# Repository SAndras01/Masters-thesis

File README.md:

# Masters-thesis
Two-axes rotary table for characterization of accelerometers

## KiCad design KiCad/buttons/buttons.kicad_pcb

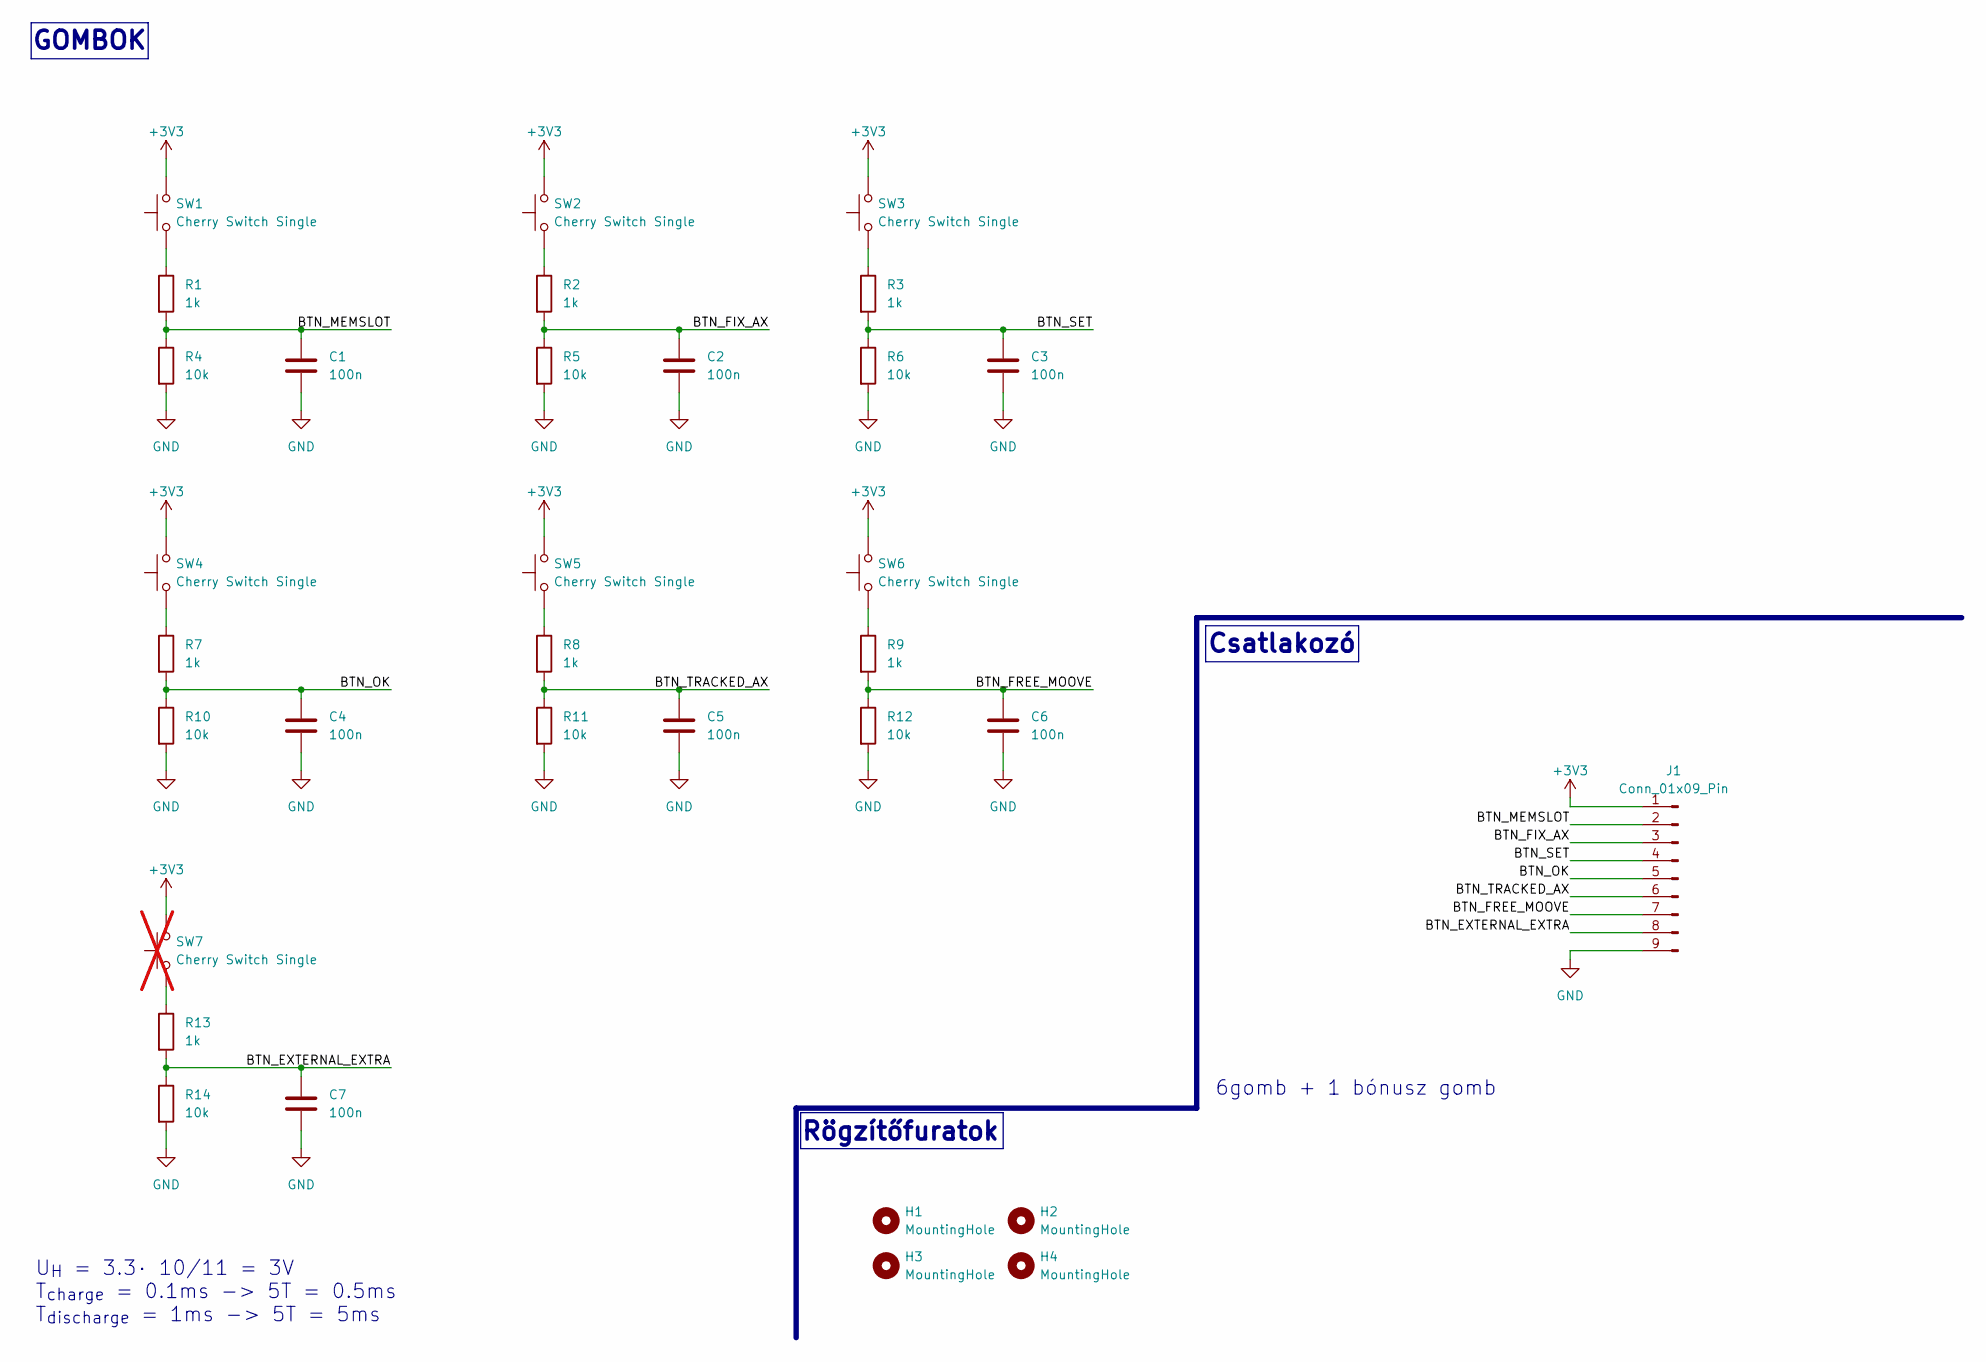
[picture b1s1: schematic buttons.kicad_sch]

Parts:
C1, C2, C3, C4, C5, C6, C7: 100n; C_0603_1608Metric
H1, H2, H3, H4: MountingHole; MountingHole_3.2mm_M3
J1: Conn_01x09_Pin; JST_PH_B9B-PH-K_1x09_P2.00mm_Vertical
R1, R2, R3, R7, R8, R9, R13: 1k; R_0603_1608Metric
R4, R5, R6, R10, R11, R12, R14: 10k; R_0603_1608Metric
SW1, SW2, SW3, SW4, SW5, SW6: Cherry Switch Single; SW_Cherry_MX_1.00u_PCB
SW7: Cherry Switch Single; SW_Cherry_MX_1.00u_PCB; not fitted

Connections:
+3V3: J1.1, SW1.2, SW2.2, SW3.2, SW4.2, SW5.2, SW6.2, SW7.2
/BTN_EXTERNAL_EXTRA: C7.1, J1.8, R13.2, R14.1
/BTN_FIX_AX: C2.1, J1.3, R2.2, R5.1
/BTN_FREE_MOOVE: C6.1, J1.7, R9.2, R12.1
/BTN_MEMSLOT: C1.1, J1.2, R1.2, R4.1
/BTN_OK: C4.1, J1.5, R7.2, R10.1
/BTN_SET: C3.1, J1.4, R3.2, R6.1
/BTN_TRACKED_AX: C5.1, J1.6, R8.2, R11.1
GND: C1.2, C2.2, C3.2, C4.2, C5.2, C6.2, C7.2, J1.9, R4.2, R5.2, R6.2, R10.2, R11.2, R12.2, R14.2
unnamed: R1.1, SW1.1
unnamed: R2.1, SW2.1
unnamed: R3.1, SW3.1
unnamed: R7.1, SW4.1
unnamed: R8.1, SW5.1
unnamed: R9.1, SW6.1
unnamed: R13.1, SW7.1

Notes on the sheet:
Rögzítőfuratok
U_{H} = 3.3· 10/11 = 3V T_{charge} = 0.1ms -> 5T = 0.5ms T_{discharge} = 1ms -> 5T = 5ms
6gomb + 1 bónusz gomb
Csatlakozó
GOMBOK

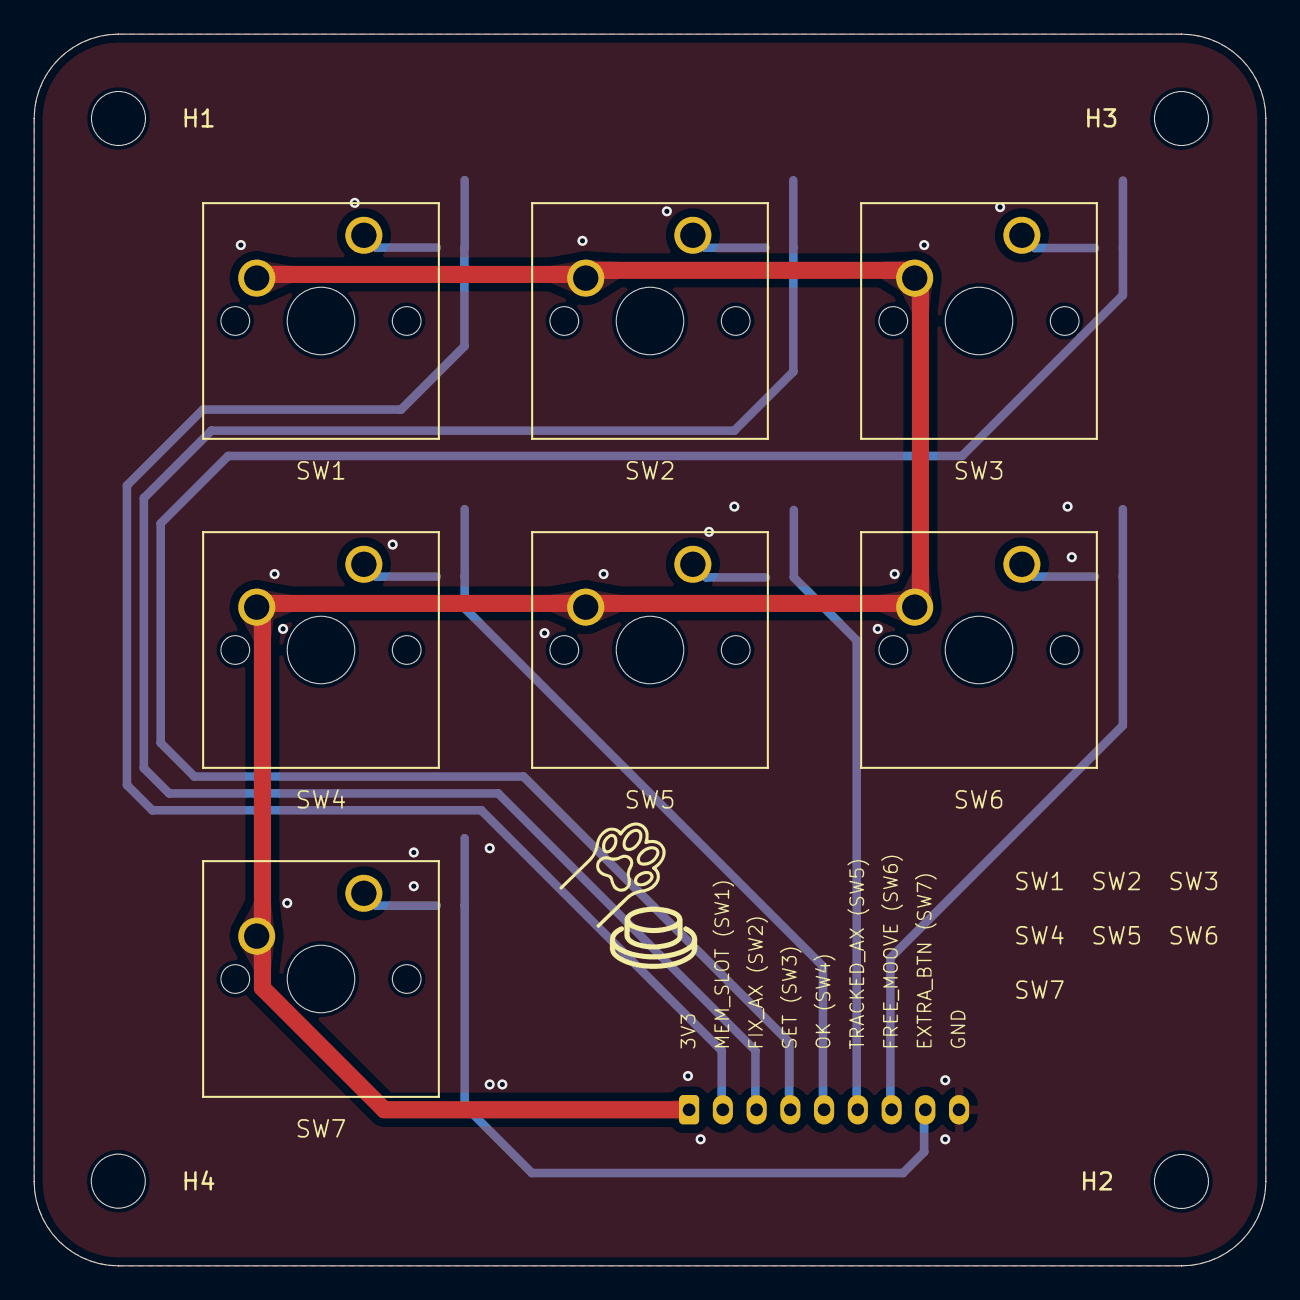
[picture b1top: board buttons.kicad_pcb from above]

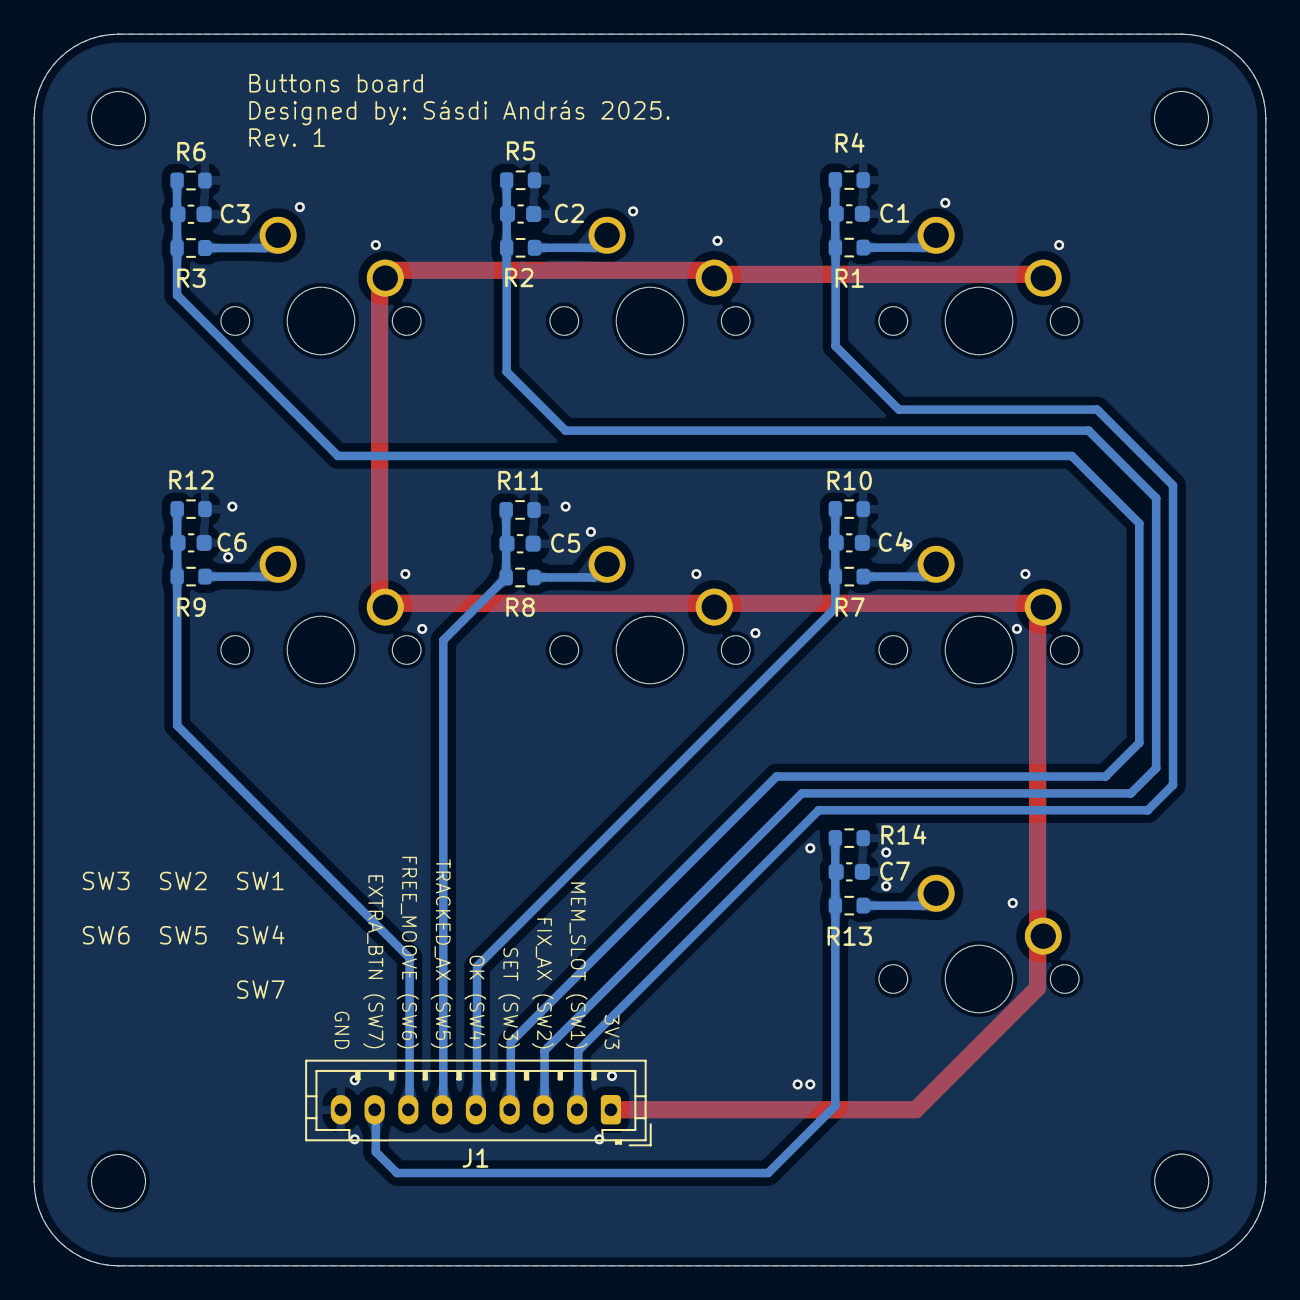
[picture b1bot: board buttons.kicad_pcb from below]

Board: 2 copper layers, 73.0 x 73.0 mm, 33 parts (22 on the bottom side), 16 nets.

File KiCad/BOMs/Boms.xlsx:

Id | Designator | Footprint | Quantity | Designation | Supplier and ref | Column1 | _1
1 | SW2,SW4,SW5,SW7,SW3,SW6,SW1 | SW_Cherry_MX_1.00u_PCB | 7 | Cherry Switch Single
2 | J1 | JST_PH_B9B-PH-K_1x09_P2.00mm_Vertical | 1 | Conn_01x09_Pin
3 | R13,R2,R1,R8,R3,R7,R9 | R_0603_1608Metric | 7 | 1k
4 | C2,C3,C6,C1,C4,C7,C5 | C_0603_1608Metric | 7 | 100n
5 | R14,R12,R5,R6,R11,R4,R10 | R_0603_1608Metric | 7 | 10k

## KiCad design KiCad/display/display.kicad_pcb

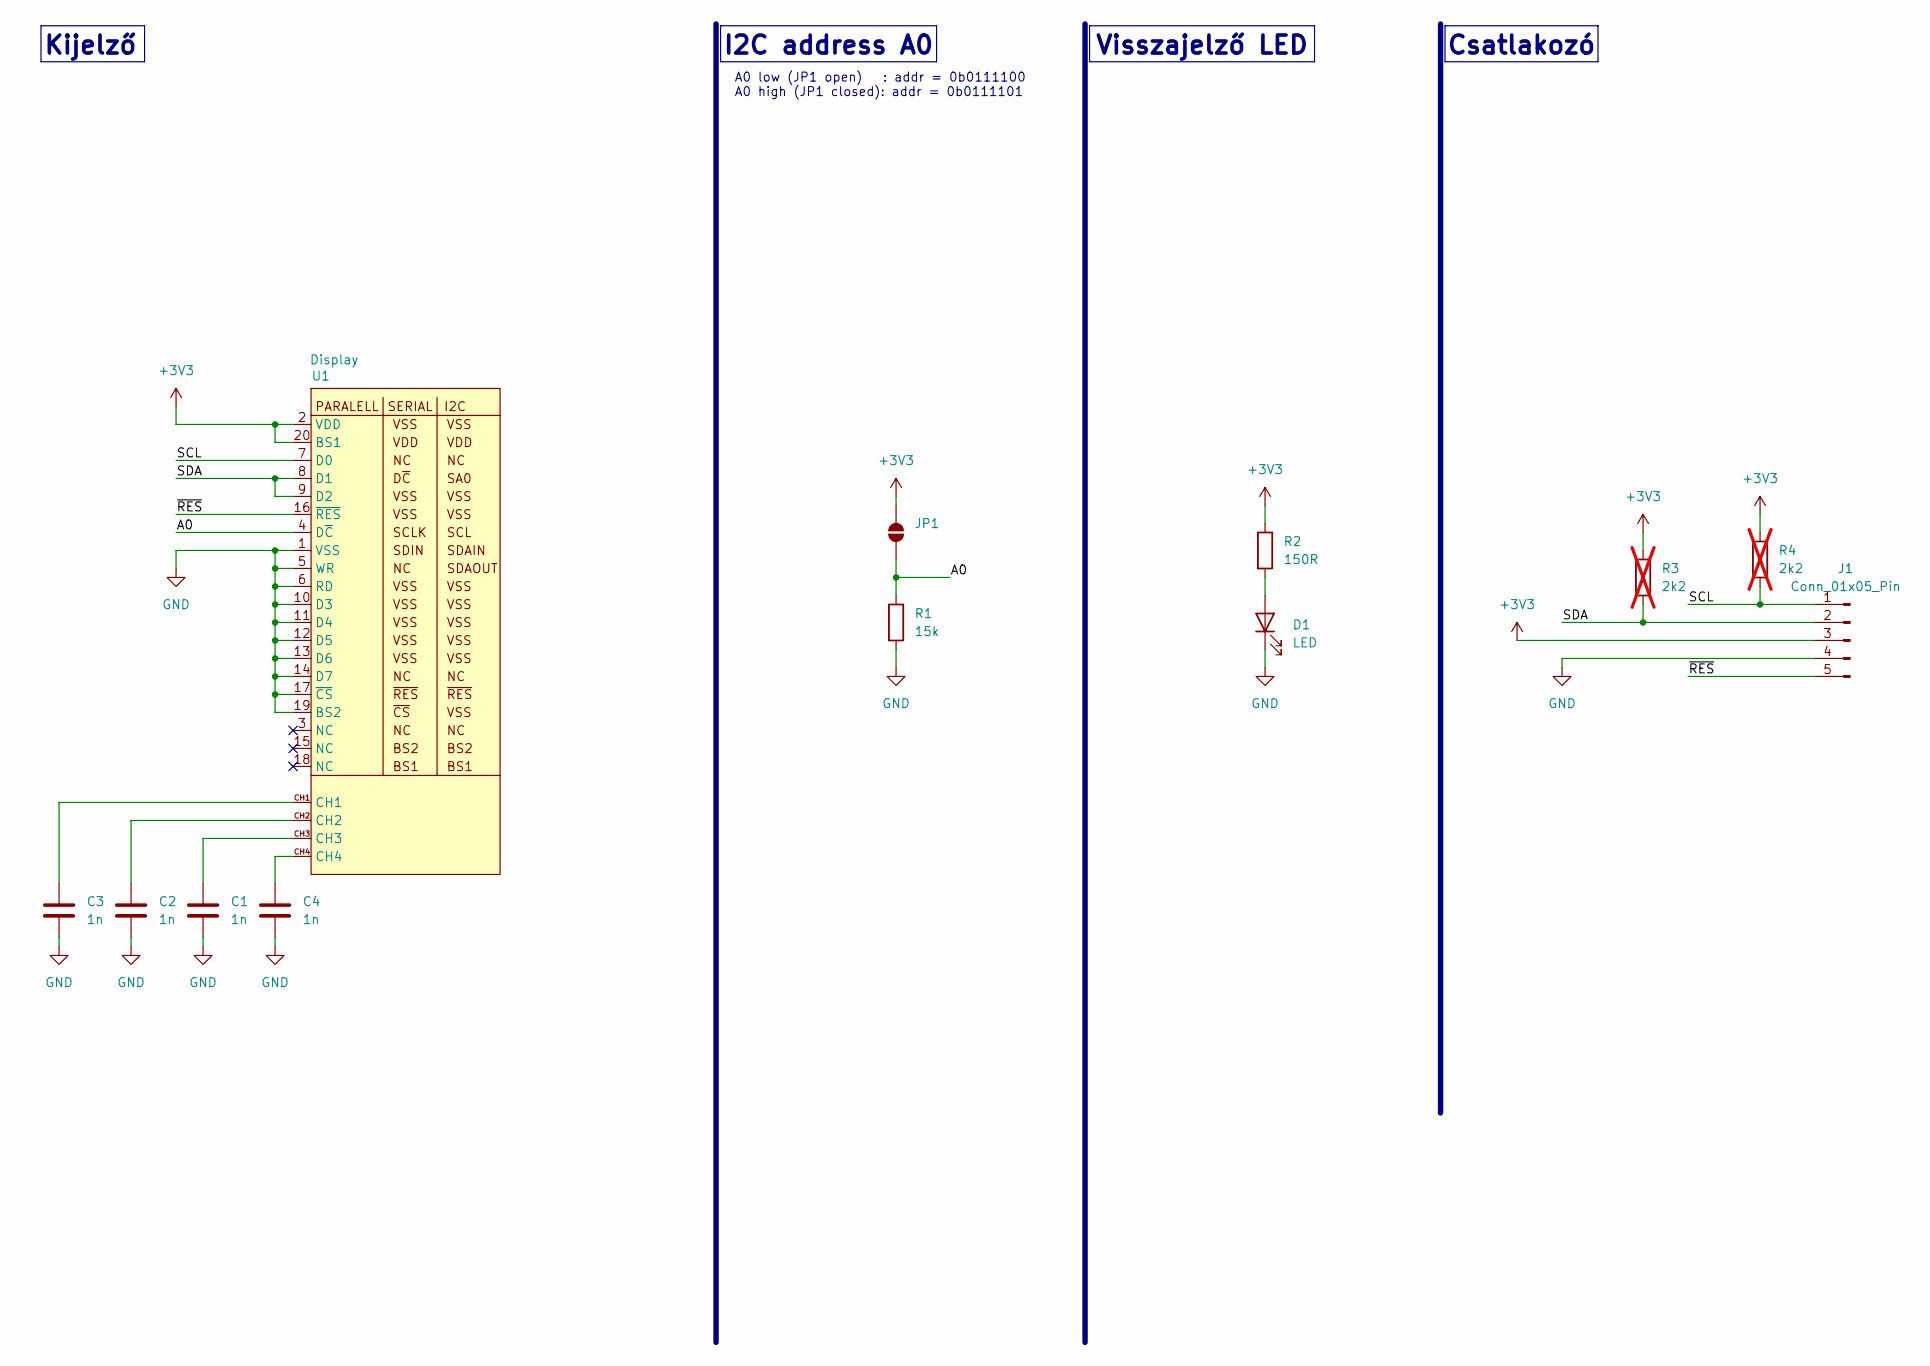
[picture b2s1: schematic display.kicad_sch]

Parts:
C1, C2, C3, C4: 1n; C_0603_1608Metric
D1: LED; D_0603_1608Metric
J1: Conn_01x05_Pin; JST_PH_B5B-PH-K_1x05_P2.00mm_Vertical
JP1: SolderJumper_2_Open; R_0603_1608Metric_Pad0.98x0.95mm_HandSolder
R1: 15k; R_0603_1608Metric_Pad0.98x0.95mm_HandSolder
R2: 150R; R_0603_1608Metric
R3, R4: 2k2; R_0603_1608Metric; not fitted
U1: Display; NHD-2.23-12832UCB3

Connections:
+3V3: J1.3, JP1.2 (B), R2.1, R3.1, R4.1, U1.2 (VDD), U1.20 (BS1)
/A0: JP1.1 (A), R1.1, U1.4 (D~C)
/SCL: J1.1, R4.2, U1.7 (D0)
/SDA: J1.2, R3.2, U1.8 (D1), U1.9 (D2)
/~RES: J1.5, U1.16 (~RES)
GND: C1.2, C2.2, C3.2, C4.2, D1.1 (K), J1.4, R1.2, U1.1 (VSS), U1.5 (WR), U1.6 (RD), U1.10 (D3), U1.11 (D4), U1.12 (D5), U1.13 (D6), U1.14 (D7), U1.17 (~CS), U1.19 (BS2)
unnamed: C1.1, U1.CH3
unnamed: C2.1, U1.CH2
unnamed: C3.1, U1.CH1
unnamed: C4.1, U1.CH4
unnamed: D1.2 (A), R2.2

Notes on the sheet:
A0 low (JP1 open) : addr = 0b0111100 A0 high (JP1 closed): addr = 0b0111101
Csatlakozó
Visszajelző LED
Kijelző
I2C address A0

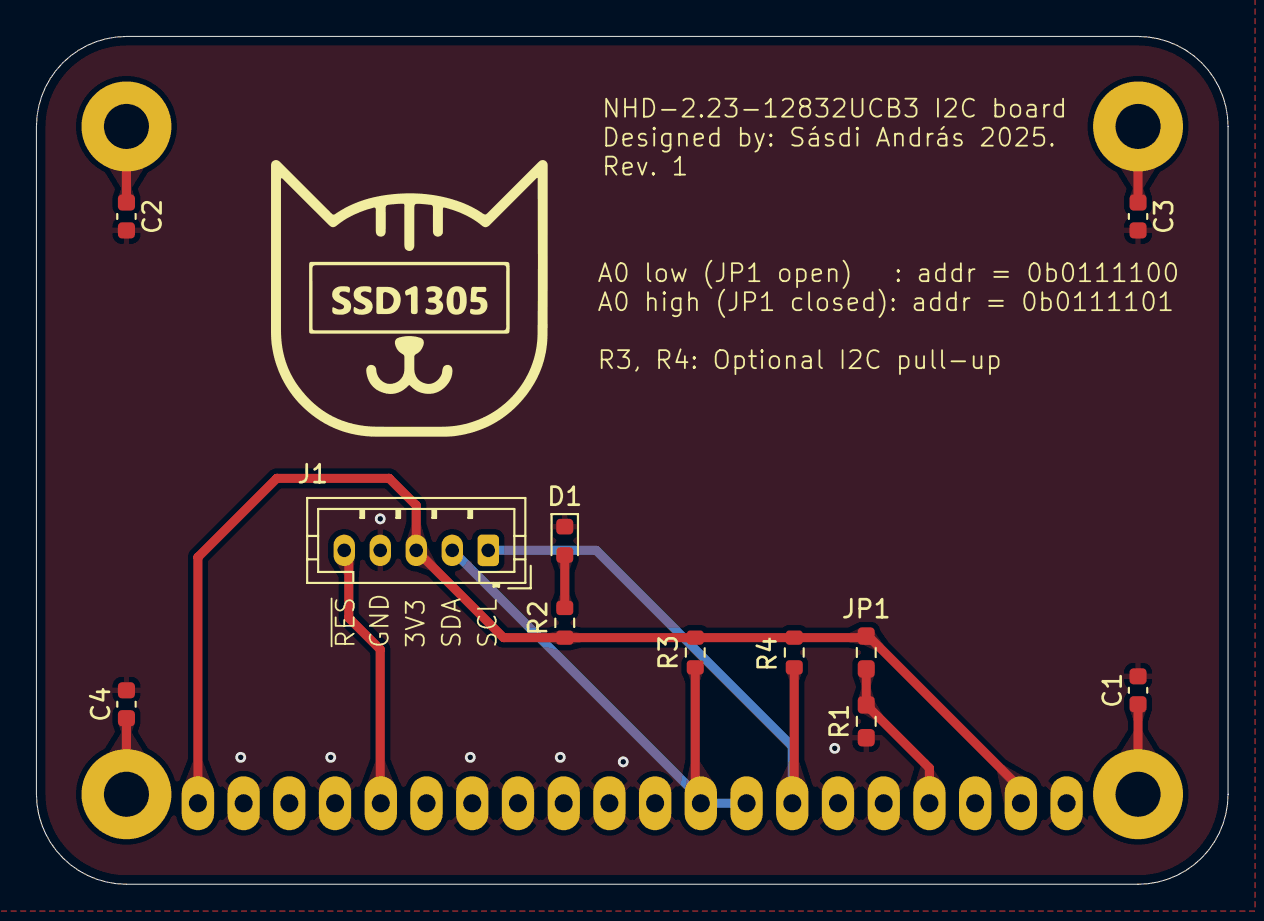
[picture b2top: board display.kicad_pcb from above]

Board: 2 copper layers, 66.2 x 47.1 mm, 12 parts (1 on the bottom side), 11 nets.

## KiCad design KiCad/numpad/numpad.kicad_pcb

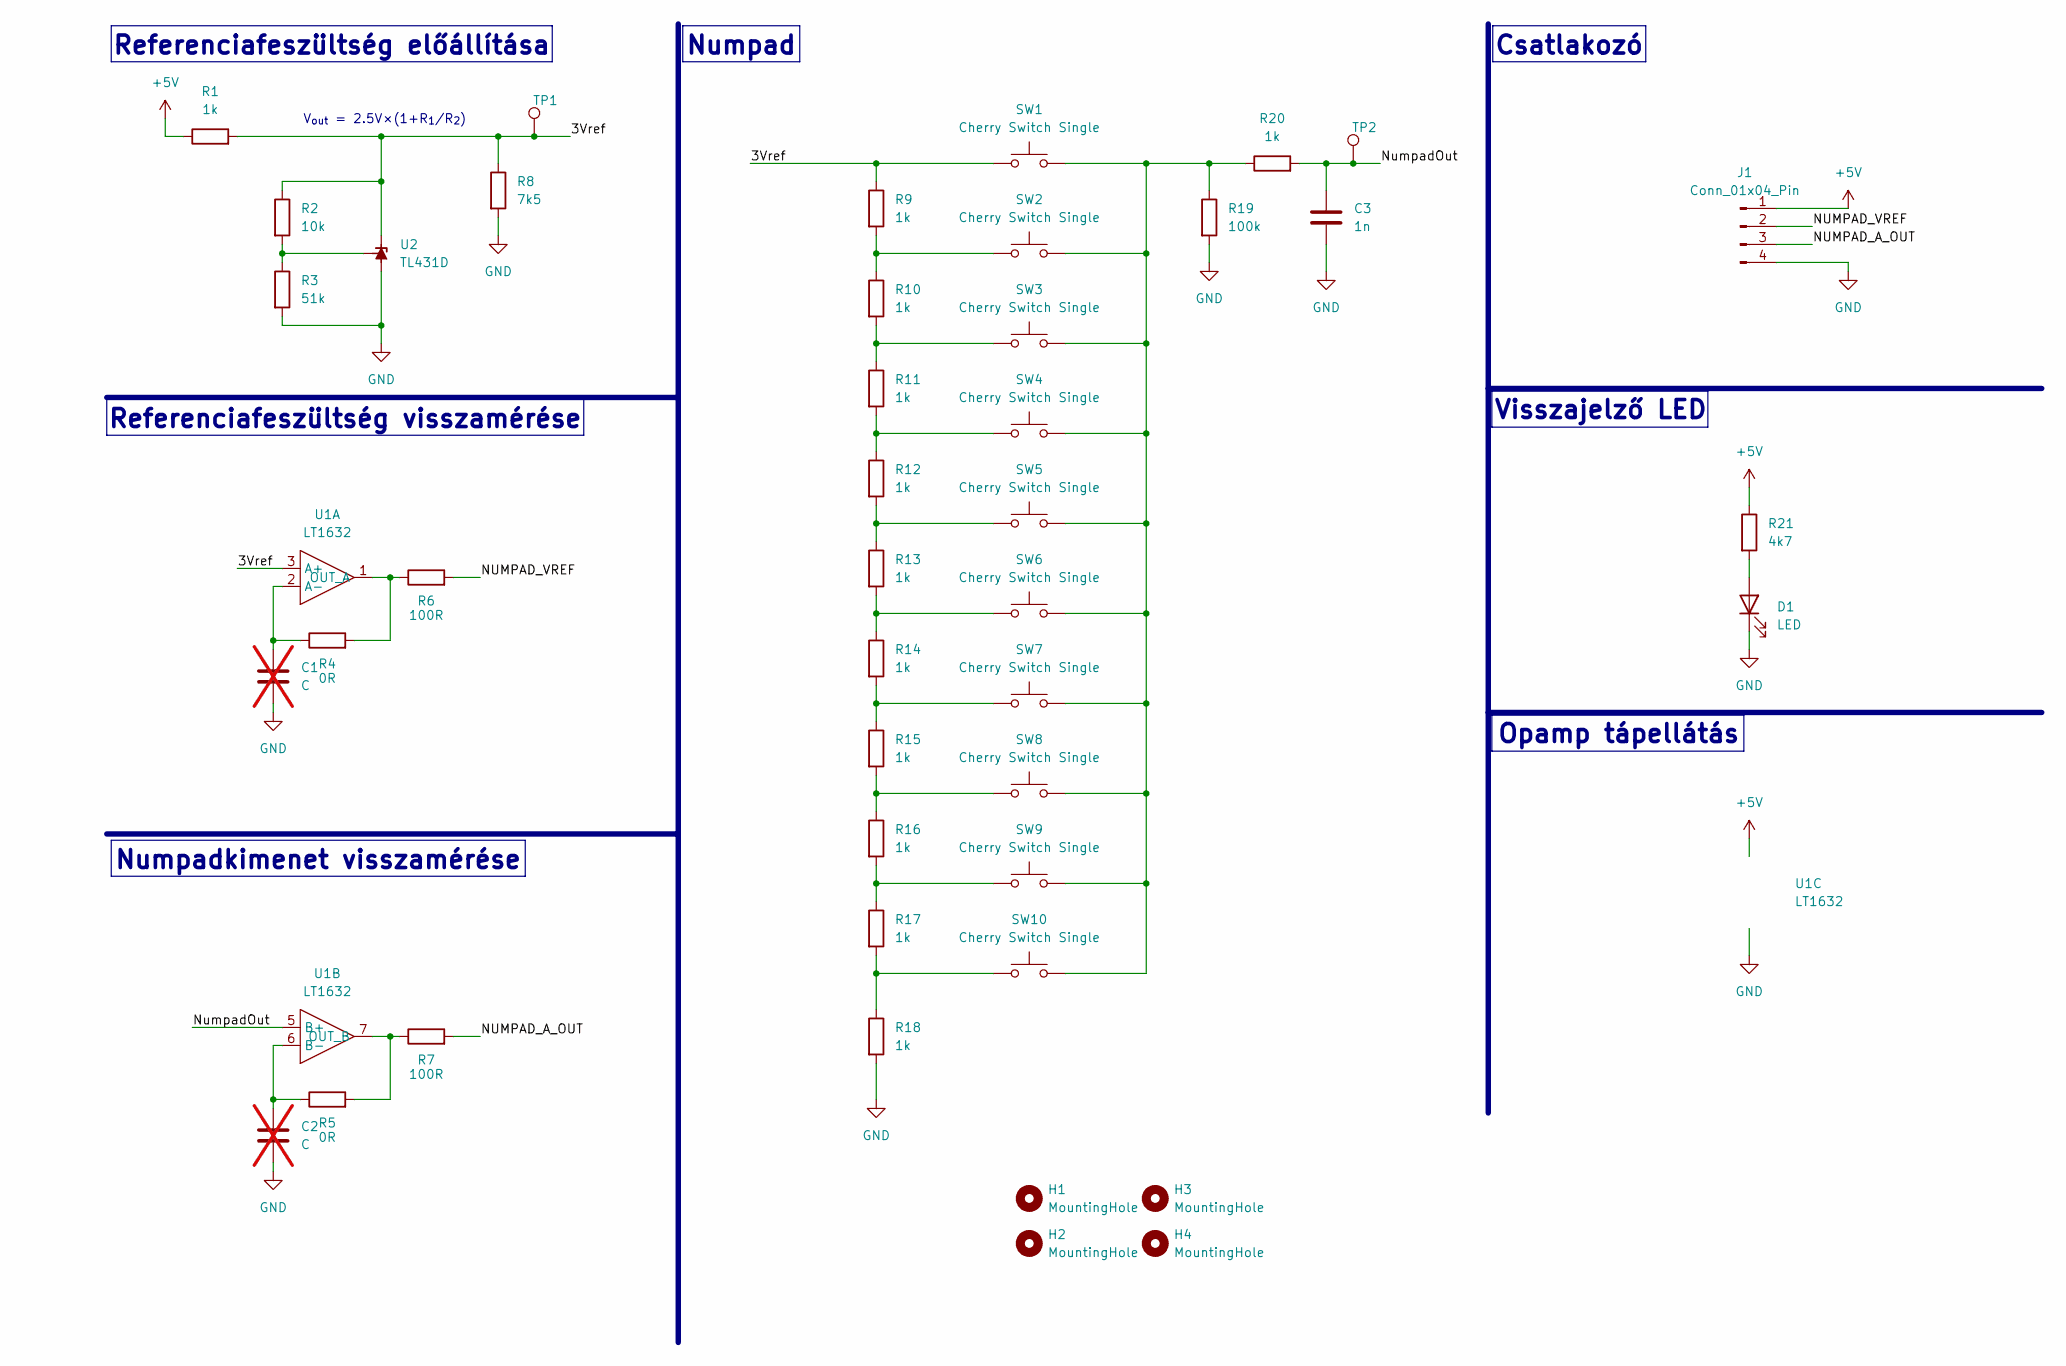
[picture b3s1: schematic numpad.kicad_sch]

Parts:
C1, C2: C; C_0603_1608Metric_Pad1.08x0.95mm_HandSolder; not fitted
C3: 1n; C_0603_1608Metric
D1: LED; D_0603_1608Metric
H1, H2, H3, H4: MountingHole; MountingHole_3.2mm_M3
J1: Conn_01x04_Pin; JST_PH_B4B-PH-K_1x04_P2.00mm_Vertical
R1, R9, R10, R11, R12, R13, R14, R15, R16, R17, R18, R20: 1k; R_0603_1608Metric
R2: 10k; R_0603_1608Metric
R3: 51k; R_0603_1608Metric
R4, R5: 0R; R_0603_1608Metric
R6, R7: 100R; R_0603_1608Metric
R8: 7k5; R_0603_1608Metric
R19: 100k; R_0603_1608Metric
R21: 4k7; R_0603_1608Metric
SW1, SW2, SW3, SW4, SW5, SW6, SW7, SW8, SW9, SW10: Cherry Switch Single; SW_Cherry_MX_1.00u_PCB
TP1, TP2: TestPoint; TestPoint_Pad_D2.0mm
U1: LT1632; SOIC-8_3.9x4.9mm_P1.27mm
U2: TL431D; SOIC-8_3.9x4.9mm_P1.27mm

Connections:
+5V: J1.1, R1.1, R21.1, U1.8 (V+)
/3Vref: R1.2, R2.1, R8.1, R9.1, SW1.1, TP1.1, U1.3 (A+), U2.1 (K)
/NUMPAD_A_OUT: J1.3, R7.2
/NUMPAD_VREF: J1.2, R6.2
/NumpadOut: C3.1, R20.2, TP2.1, U1.5 (B+)
GND: C1.2, C2.2, C3.2, D1.1 (K), J1.4, R3.2, R8.2, R18.2, R19.2, U1.4 (V-), U2.2 (A), U2.3 (A), U2.6 (A), U2.7 (A)
unnamed: D1.2 (A), R21.2
unnamed: R9.2, R10.1, SW2.1
unnamed: R10.2, R11.1, SW3.1
unnamed: R11.2, R12.1, SW4.1
unnamed: R12.2, R13.1, SW5.1
unnamed: R13.2, R14.1, SW6.1
unnamed: R14.2, R15.1, SW7.1
unnamed: R15.2, R16.1, SW8.1
unnamed: R16.2, R17.1, SW9.1
unnamed: R17.2, R18.1, SW10.1
unnamed: R19.1, R20.1, SW1.2, SW2.2, SW3.2, SW4.2, SW5.2, SW6.2, SW7.2, SW8.2, SW9.2, SW10.2
unnamed: C1.1, R4.1, U1.2 (A-)
unnamed: R4.2, R6.1, U1.1 (OUT_A)
unnamed: C2.1, R5.1, U1.6 (B-)
unnamed: R5.2, R7.1, U1.7 (OUT_B)
unnamed: R2.2, R3.1, U2.8 (REF)

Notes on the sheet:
Visszajelző LED
Referenciafeszültség előállítása
Referenciafeszültség visszamérése
Numpadkimenet visszamérése
Numpad
V_{out} = 2.5V×(1+R_{1}/R_{2})
Csatlakozó
Opamp tápellátás

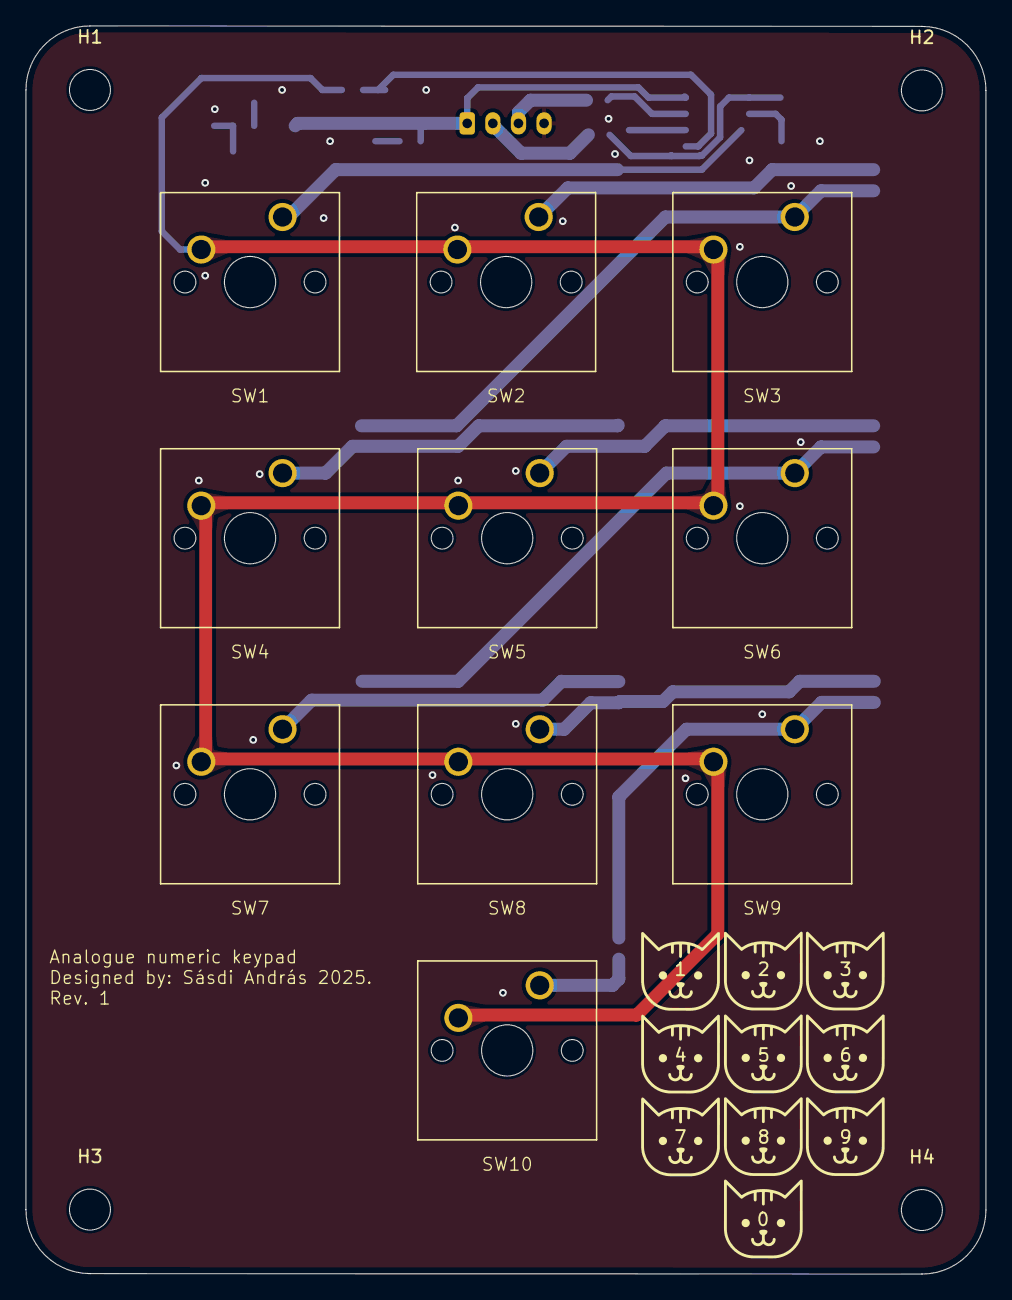
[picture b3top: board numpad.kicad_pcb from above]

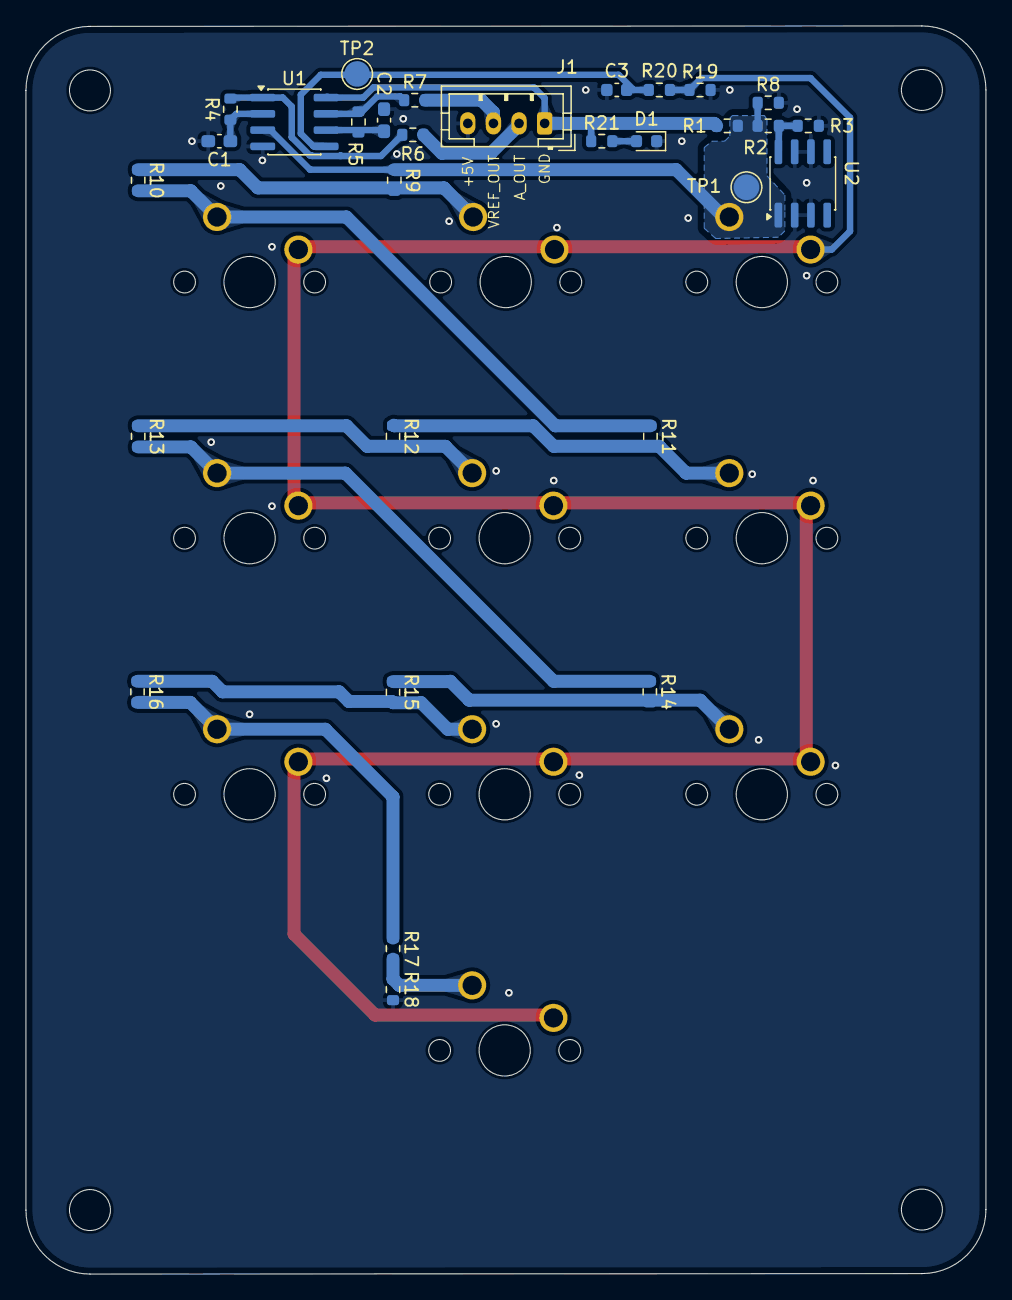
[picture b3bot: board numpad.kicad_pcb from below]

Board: 2 copper layers, 75.0 x 97.5 mm, 44 parts (30 on the bottom side), 22 nets.

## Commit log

2025-08-27 Progress uploaded
    Progress so far: Stepper controller
2025-08-27 gitignore
2025-08-27 metadata deleted
2025-08-27 .settings removed
2025-08-27 reupload
2025-09-05 OLED driver
2025-09-07 OLED driver finished
2025-09-08 Doxygen added, OLED documentation started, tests for grayscale
2025-09-14 User interface started
    IDE updated during work, I hope it wont break the whole project on the other computer
2025-09-15 file system management
    LUT python scripts put into correct subfolder
2025-09-16 StateMachine and user interface
2025-09-17 OOP state machine
    Állapotgép megvalósítása objektum orientáltan az állapotok egyszerűbb kezelhetősége érdekében
2025-09-17 State machine updated
    So far only the "StateSetFixTrackDeg" state is implemented. Also it should be named smth better, like "SetParams", as we are setting all the params of a memory slot here. Also an eeprom should be int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
2025-09-24 Memory started
2025-09-24 UI removed, as it is being developed in "State machine"
2025-09-24 File diffs caused by building
2025-09-24 diffs caused by building
2025-10-01 Shellminator added
2025-10-03 Debug added to gitignore
2025-10-06 Accelerometer driver, regmap added, testing in main.cpp
2025-10-08 AS5147U dev started
2025-10-10 encoder dev con.
2025-10-10 AS5147U calss added
2025-10-12 Accelerometer driver continued
2025-10-21 Migration to bigger board
2025-10-22 eeprom comm error debug
2025-10-26 eeprom debug completed, hw design started
2025-11-02 numpad schematic started
2025-11-02 KiCad simulations, numpad design
2025-11-02 kicad saves
2025-11-03 Display and numpad schematics
2025-11-03 gitignore update
    LTspice .raw files contain simulation data, that can always be calculated locally, version control is not needed
2025-11-03 Work on schematics
2025-11-04 Buttons module and main board schematics
2025-11-06 Main sch further development
2025-11-06 MAIN board schematic mostly done
2025-11-08 schematics finished
2025-11-09 Dokumentáció elkezdve
2025-11-10 PCB designs started
2025-11-11 numpad, buttons, display PCB done, review needed
2025-11-11 main board pcb design started
2025-11-12 main board pcb continued
2025-11-13 motherboard pcb layout (MCU)
2025-11-13 Unnecessary silkscreen markings moveed to user1 layer. next step is routing and writing pin names for easier future debugging
2025-11-15 motherboard PCB design
2025-11-16 motherboard PCCB done, review needed
2025-11-16 documentation
2025-11-19 PCB bugfixes based on review
2025-11-22 motor controll documentation
2025-11-22 documentation continued
2025-11-23 Dokumentation cont, added some comment to the state machine
2025-11-24 Documentation + BOM
2025-11-28 documentation, OLED demo, BOM
2025-12-01 documentation and plots
2025-12-01 save files
2025-12-03 documentation and code documentation
2025-12-04 doxyfile
2025-12-04 images added
2025-12-07 docs
2025-12-17 Tanszéki kérések javítva
2025-12-18 docx véglegesítve
2025-12-18 small adjustments
2025-12-18 exports
2026-01-14 Power point continued
2026-01-15 ppt continued
2026-01-19 prezentáció folytatva
2026-01-20 Prezi befejezve
2026-01-22 slide comments
